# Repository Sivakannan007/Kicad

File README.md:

View this project on [CADLAB.io](https://cadlab.io/project/29334). 

# Kicad

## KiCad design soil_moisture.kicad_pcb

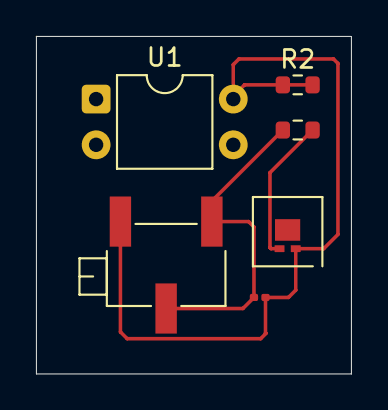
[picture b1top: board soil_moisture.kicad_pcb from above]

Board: 2 copper layers, 17.5 x 18.8 mm, 6 parts (0 on the bottom side), 3 nets.

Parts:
D1: LED; LED-L1T2_LUMILEDS
R1: R; R_0201_0603Metric
R2, R3: R; R_0603_1608Metric
RV1: R_Potentiometer; Potentiometer_Bourns_3269X_Horizontal
U1: LM393; DIP-4_W7.62mm

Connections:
/gnd: D1.1 (K), R1.2, R2.1, R2.2, RV1.3, U1.4 (V-)
/vcc: R1.1, R3.1, RV1.1, RV1.2
unnamed: D1.2 (A), R3.2

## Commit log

2025-04-30 Assignment
2025-04-30 Backlink to CADLAB.io has been added.
